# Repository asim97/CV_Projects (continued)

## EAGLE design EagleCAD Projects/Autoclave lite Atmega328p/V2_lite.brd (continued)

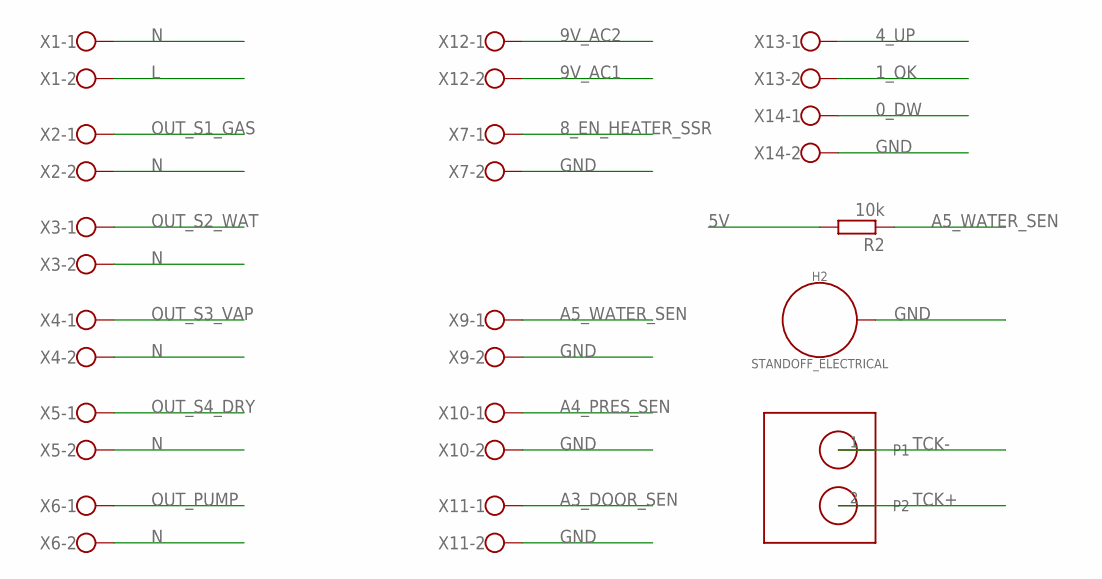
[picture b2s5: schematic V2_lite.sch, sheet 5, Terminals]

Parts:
H2: STANDOFF_ELECTRICAL; STANDOFF-ELECTRICAL
R2: 10k; 0207/10
U$2: THERMO_CONNECT; HW-550
X1, X2, X3, X4, X5, X6, X7, X9, X10, X11, X12, X13, X14: W237-102

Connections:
0_DW: X14.1; also elsewhere on the board
1_OK: X13.2; also elsewhere on the board
4_UP: X13.1; also elsewhere on the board
5V: R2.2; also elsewhere on the board
8_EN_HEATER_SSR: X7.1; also elsewhere on the board
9V_AC1: X12.2; also elsewhere on the board
9V_AC2: X12.1; also elsewhere on the board
A3_DOOR_SEN: X11.1; also elsewhere on the board
A4_PRES_SEN: X10.1; also elsewhere on the board
A5_WATER_SEN: R2.1, X9.1; also elsewhere on the board
GND: H2.P1, X7.2, X9.2, X10.2, X11.2, X14.2; also elsewhere on the board
L: X1.2; also elsewhere on the board
N: X1.1, X2.2, X3.2, X4.2, X5.2, X6.2
OUT_PUMP: X6.1; also elsewhere on the board
OUT_S1_GAS: X2.1; also elsewhere on the board
OUT_S2_WAT: X3.1; also elsewhere on the board
OUT_S3_VAP: X4.1; also elsewhere on the board
OUT_S4_DRY: X5.1; also elsewhere on the board
TCK+: U$2.2; also elsewhere on the board
TCK-: U$2.1; also elsewhere on the board

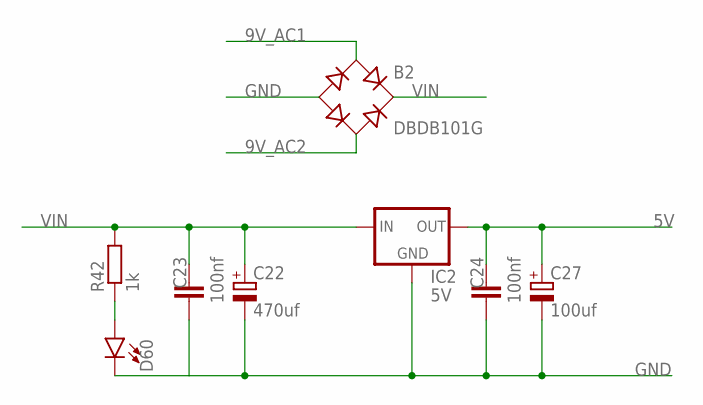
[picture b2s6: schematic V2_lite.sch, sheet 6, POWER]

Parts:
B2: DBDB101G; DB
C22: 470uf; E3,5-8
C23, C24: 100nf; C050-030X075
C27: 100uf; E3,5-8
D60: LED5MM; LED_5MM
IC2: 5V; 78XXL
R42: 1k; 0207/10

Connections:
5V: C24.2, C27.+, IC2.OUT; also elsewhere on the board
9V_AC1: B2.AC1; also elsewhere on the board
9V_AC2: B2.AC2; also elsewhere on the board
GND: B2.-, C22.-, C23.1, C24.1, C27.-, D60.K (C), IC2.GND; also elsewhere on the board
unnamed: D60.A, R42.1
VIN: B2.+, C22.+, C23.2, IC2.IN, R42.2

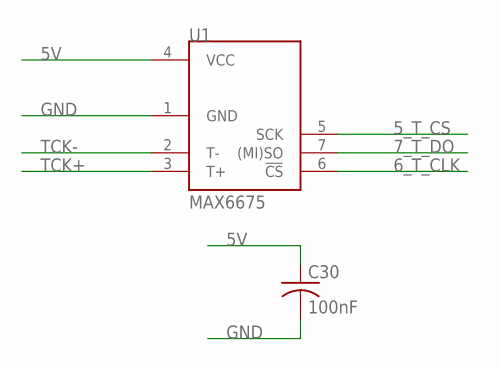
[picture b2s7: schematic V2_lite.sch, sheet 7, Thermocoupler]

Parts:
C30: 100nF; C050-035X075
U1: MAX6675; SOIC8

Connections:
5V: C30.1, U1.4 (VCC); also elsewhere on the board
5_T_CS: U1.5 (SCK); also elsewhere on the board
6_T_CLK: U1.6 (!CS); also elsewhere on the board
7_T_DO: U1.7 ((MI)SO); also elsewhere on the board
GND: C30.2, U1.1 (GND); also elsewhere on the board
TCK+: U1.3 (T+); also elsewhere on the board
TCK-: U1.2 (T-); also elsewhere on the board

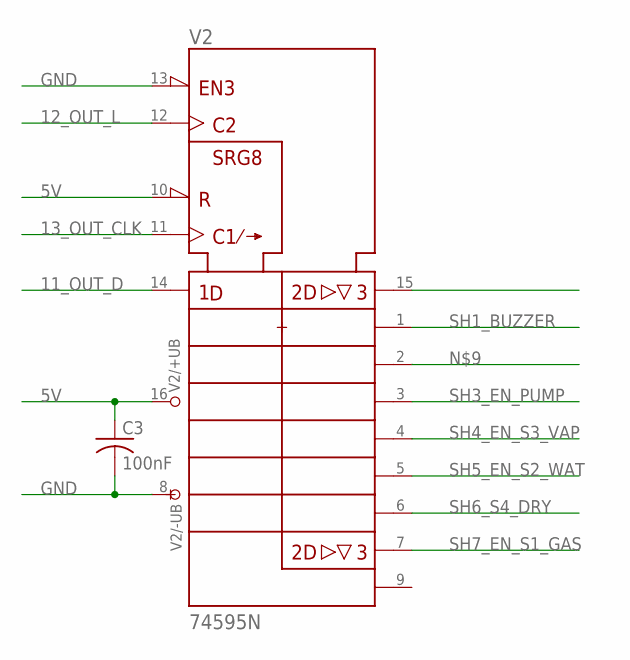
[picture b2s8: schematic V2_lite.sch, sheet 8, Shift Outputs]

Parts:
C3: 100nF; C050-035X075
V2: 74595N; DIL16

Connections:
5V: C3.1, V2.10 (!SRCLR), V2.16 (+UB); also elsewhere on the board
11_OUT_D: V2.14 (SER); also elsewhere on the board
12_OUT_L: V2.12 (RCK); also elsewhere on the board
13_OUT_CLK: V2.11 (SRCK); also elsewhere on the board
GND: C3.2, V2.8 (-UB), V2.13 (!G); also elsewhere on the board
SH1_BUZZER: V2.1 (QB); also elsewhere on the board
SH3_EN_PUMP: V2.3 (QD); also elsewhere on the board
SH4_EN_S3_VAP: V2.4 (QE); also elsewhere on the board
SH5_EN_S2_WAT: V2.5 (QF); also elsewhere on the board
SH6_S4_DRY: V2.6 (QG); also elsewhere on the board
SH7_EN_S1_GAS: V2.7 (QH); also elsewhere on the board

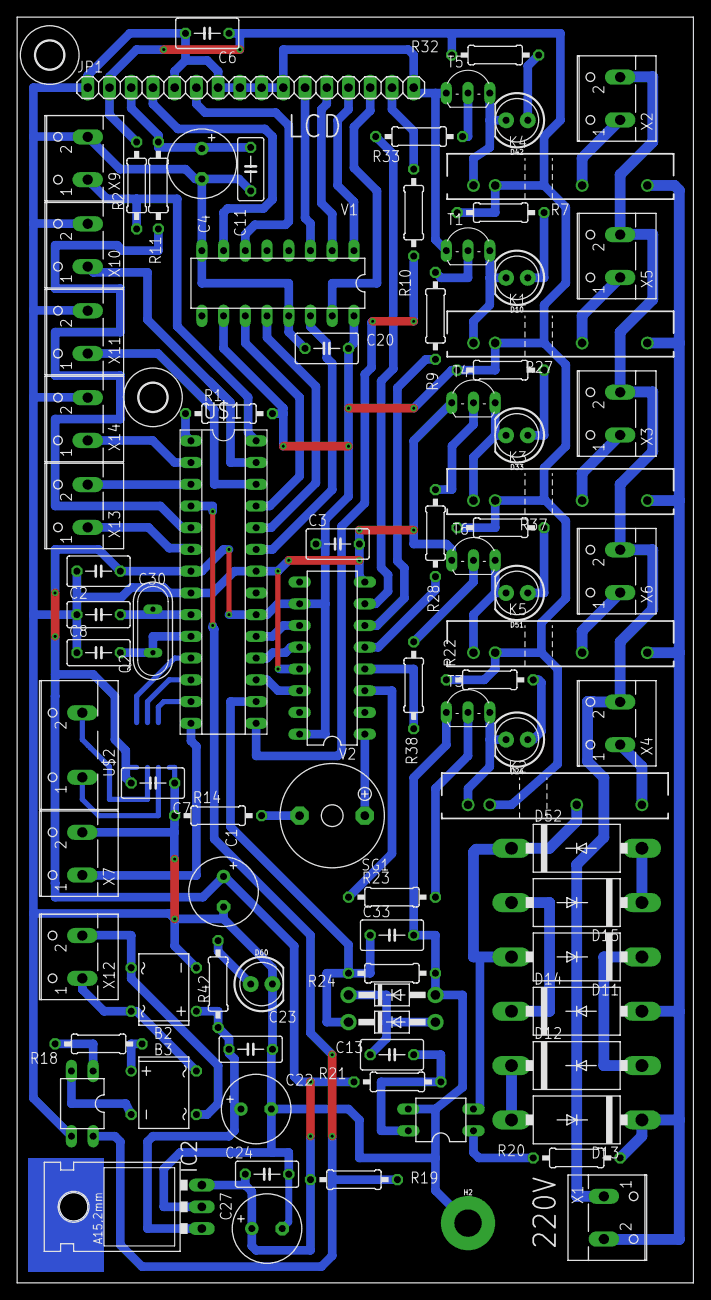
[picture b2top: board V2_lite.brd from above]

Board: 2 copper layers, 79.0 x 147.9 mm, 90 parts (1 on the bottom side), 79 nets.
